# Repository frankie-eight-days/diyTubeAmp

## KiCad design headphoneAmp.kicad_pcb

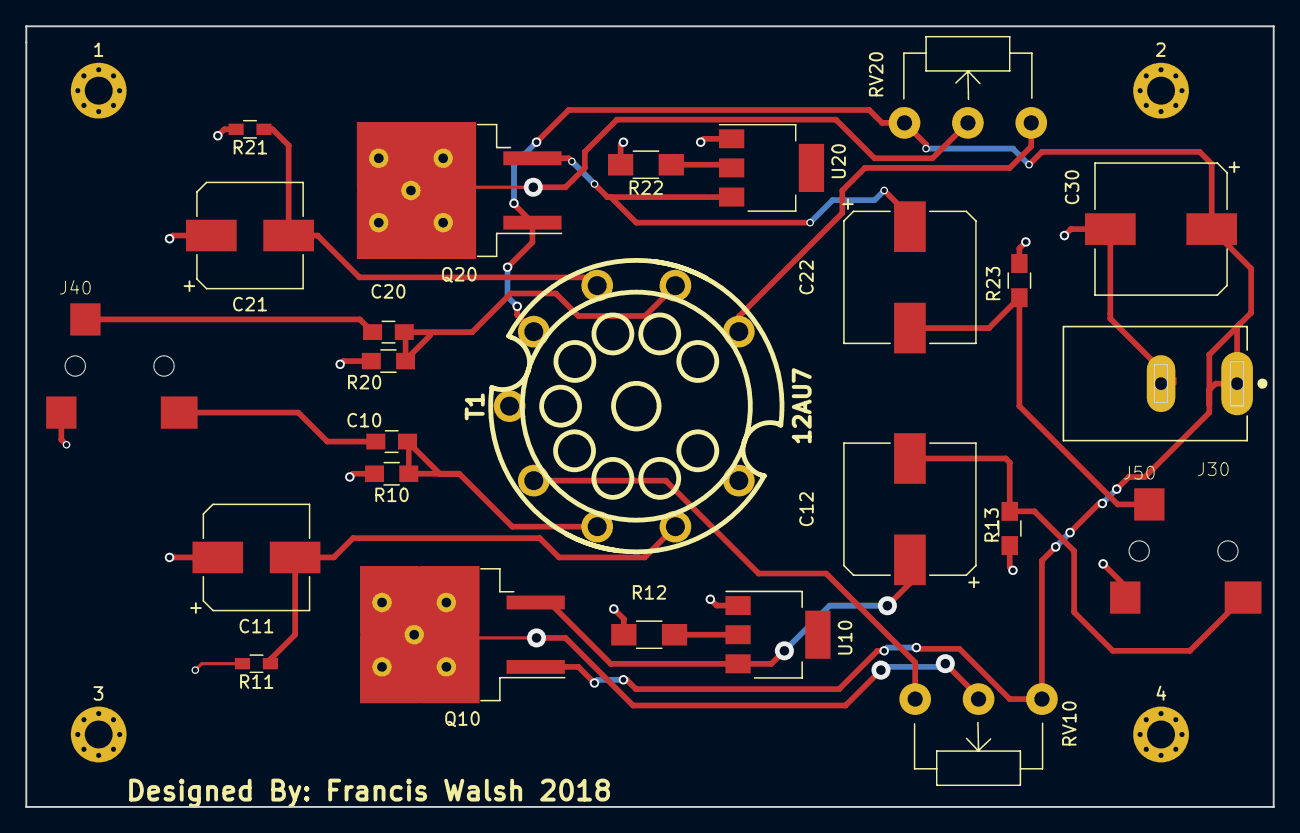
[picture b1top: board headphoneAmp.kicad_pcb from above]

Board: 2 copper layers, 98.4 x 61.6 mm, 29 parts (0 on the bottom side), 18 nets.

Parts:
1, 2, 3, 4: MountingHole_2.2mm_M2_Pad_Via
C10, C20: 2.2u; C_0805_HandSoldering
C11, C21: 100u; CP_Elec_8x10.5
C12, C22, C30: 470u; CP_Elec_10x10.5
J30: CUI_PJ-037B
J40, J50: CUI_SJ-3523-SMT-TR
Q10, Q20: TO-263-2
R10, R20: 100k; R_0805_HandSoldering
R11, R21: 150; R_0603_HandSoldering
R12, R22: 10; R_1206_HandSoldering
R13, R23: 1k; R_0805_HandSoldering
RV10, RV20: 50k; Potentiometer_WirePads_largePads
T1: 12AU7; socket_gzc9-b
U10, U20: SOT-223

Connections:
/12_6V: C30.1, J30.1, Q10.1, Q20.1, RV10.1, RV20.1, T1.4
/l_c_post: RV20.3, T1.1
/left_channel: C20.2, J40.3
/output_left_channel: C22.2, J50.3, R23.2
/output_right_channel: C12.2, J50.2, R13.2
/right_c_tube: C10.1, R10.1, T1.7
/right_channel: C10.2, J40.2
GND: 1.1, 2.2, 3.1, 4.1, C11.1, C21.1, C30.2, J30.2, J40.1, J50.1, R10.2, R11.2, R12.2, R13.1, R20.2, R21.2, R22.2, R23.1, T1.5, U10.1, U20.1
unnamed: C11.2, R11.1, T1.8
unnamed: C12.1, Q10.3, U10.3
unnamed: C20.1, R20.1, T1.2
unnamed: C21.2, R21.1, T1.3
unnamed: C22.1, Q20.3, U20.3
unnamed: Q10.2, RV10.2
unnamed: Q20.2, RV20.2
unnamed: R12.1, U10.2
unnamed: R22.1, U20.2
unnamed: RV10.3, T1.6

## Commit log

2018-07-28 Golden... (maybe)
